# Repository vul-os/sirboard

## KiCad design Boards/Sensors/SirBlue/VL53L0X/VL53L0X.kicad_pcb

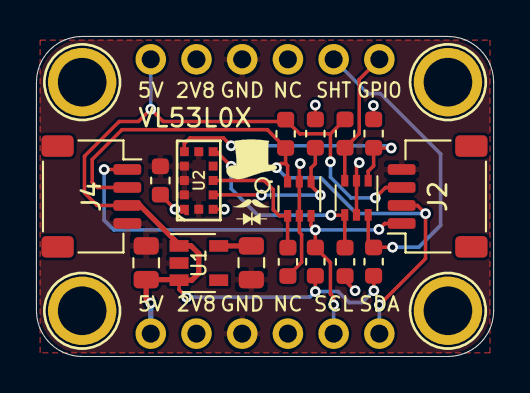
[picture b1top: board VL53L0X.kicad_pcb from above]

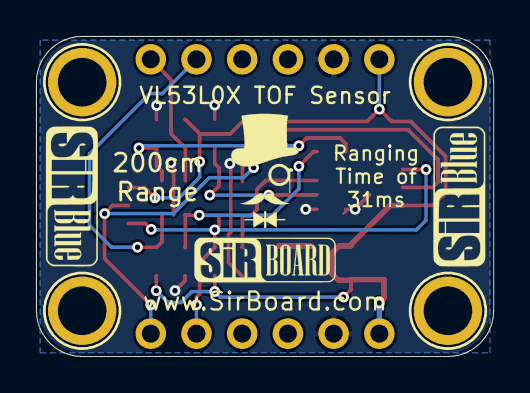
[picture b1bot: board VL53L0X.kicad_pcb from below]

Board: 2 copper layers, 25.4 x 17.8 mm, 23 parts (2 on the bottom side), 12 nets.

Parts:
C1, C4: 10uF; C_0805_2012Metric
C2: 100nF; C_0603_1608Metric
H1, H2, H3, H4: MountingHole; MountingHole_M2.5_SirBoard
J1, J3: Conn_01x06; PinHeader_1x06_P2.54mm_Vertical
J2, J4: Conn_01x04; JST_SH_SM04B-SRSS-TB_1x04-1MP_P1.00mm_Horizontal
Q1, Q2: BSS138DW; SOT-363_SC-70-6
R1, R2, R3, R4, R5, R6, R7, R8: 10K; R_0603_1608Metric
U1: AP2127K-2.8; SOT-23-5
U2: VL53L0X; LGA-12-2.4X4.4

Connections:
2V8: C2.1, J1.2, J3.2, Q1.2, Q1.5, Q2.2, Q2.5, R1.2, R3.2, R5.2, R7.2, U2.1, U2.11
5V: C1.1, J1.1, J2.3, J3.1, J4.3, R2.1, R4.1, R6.1, R8.1, U1.1, U1.3
GND: C1.2, C2.2, C4.2, J1.3, J2.4, J3.3, J4.4, U1.2, U2.2, U2.3, U2.4, U2.6, U2.12
GPIO_2V8: Q1.4, R3.1, U2.7
GPIO_5V: J3.6, Q1.3, R4.2
unnamed: C4.1, U1.5
SCL_2V8: Q2.1, R5.1, U2.10
SCL_5V: J1.5, J2.1, J4.1, Q2.6, R6.2
SDA_2V8: Q2.4, R7.1, U2.9
SDA_5V: J1.6, J2.2, J4.2, Q2.3, R8.2
XSHUT_2V8: Q1.1, R1.1, U2.5
XSHUT_5V: J3.5, Q1.6, R2.2

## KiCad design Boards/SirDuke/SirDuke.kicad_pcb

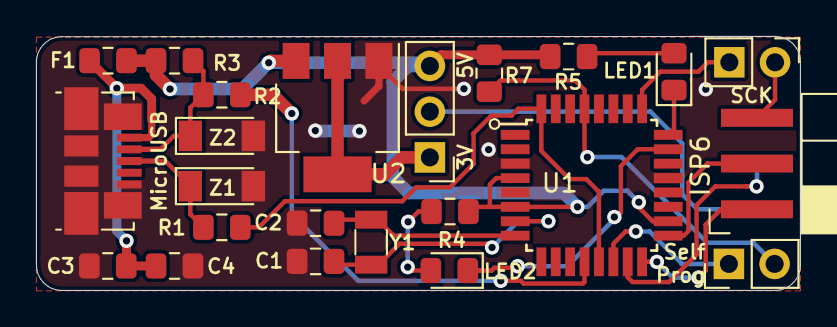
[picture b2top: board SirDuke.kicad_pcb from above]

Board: 2 copper layers, 42.4 x 14.1 mm, 23 parts (0 on the bottom side), 22 nets.

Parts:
3V      5V: Conn_01x03; PinHeader_1x03_P2.54mm_Vertical
C1, C2: 18pF; C_0805_2012Metric_Pad1.15x1.40mm_HandSolder
C3: 100nF; C_0805_2012Metric_Pad1.15x1.40mm_HandSolder
C4: 4u7; C_0805_2012Metric_Pad1.15x1.40mm_HandSolder
F1: 500mA; R_0805_2012Metric_Pad1.15x1.40mm_HandSolder
ISP6: Conn_02x03_Odd_Even; PinSocket_2x03_P2.54mm_Horizontal_SMD
LED1: G; LED_0805_2012Metric_Pad1.15x1.40mm_HandSolder
LED2: R; LED_0805_2012Metric_Pad1.15x1.40mm_HandSolder
MicroUSB: USB_B_Micro; USB_Micro-B_Molex_47346-0001
R1, R2: 68e; R_0805_2012Metric_Pad1.15x1.40mm_HandSolder
R3: 2k2; R_0805_2012Metric_Pad1.15x1.40mm_HandSolder
R4, R5: 1k; R_0805_2012Metric_Pad1.15x1.40mm_HandSolder
R7: 10k; R_0805_2012Metric_Pad1.15x1.40mm_HandSolder
SCK: Conn_01x02; PinHeader_1x02_P2.54mm_Vertical
SelfProg: Conn_01x02; PinHeader_1x02_P2.54mm_Vertical
U1: ATmega8-16AU; TQFP-32_7x7mm_P0.8mm
U2: AMS1117-3.3; SOT-223-3_TabPin2
Y1: Crystal; Crystal_SMD_3215-2Pin_3.2x1.5mm
Z1, Z2: 3.6V; D_MiniMELF

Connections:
unnamed: C1.1, C2.2, C3.2, C4.2, ISP6.6, MicroUSB.5, MicroUSB.6, U1.3, U1.5, U1.21, U2.1, Z1.2, Z2.2
unnamed: C1.2, U1.7, Y1.1
unnamed: C2.1, U1.8, Y1.2
unnamed: C3.1, C4.1, F1.2, MicroUSB.1
unnamed: 3V 5V.3, F1.1, R3.1, R4.1, R5.1, R7.2, U1.4, U1.6, U1.18, U2.3
unnamed: 3V 5V.1, U2.2
unnamed: 3V 5V.2, ISP6.2
unnamed: ISP6.5, SCK.1
unnamed: SCK.2, U1.25
unnamed: SelfProg.1, U1.14
unnamed: R7.1, SelfProg.2, U1.29
unnamed: MicroUSB.2, R2.2, R3.2, Z2.1
unnamed: MicroUSB.3, R1.2, Z1.1
unnamed: ISP6.1, U1.16
unnamed: ISP6.3, U1.17
unnamed: ISP6.4, U1.15
unnamed: LED1.1, U1.24
unnamed: LED1.2, R5.2
unnamed: LED2.1, U1.23
unnamed: LED2.2, R4.2
unnamed: R1.1, U1.13, U1.32
unnamed: R2.1, U1.12

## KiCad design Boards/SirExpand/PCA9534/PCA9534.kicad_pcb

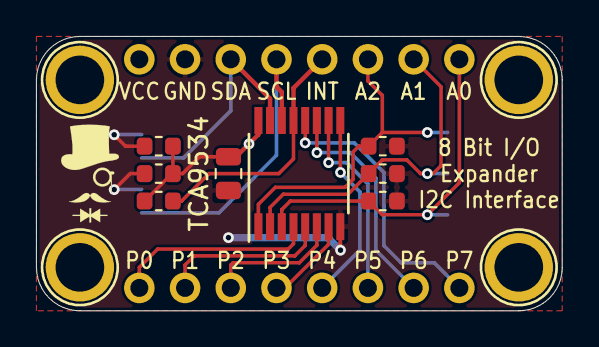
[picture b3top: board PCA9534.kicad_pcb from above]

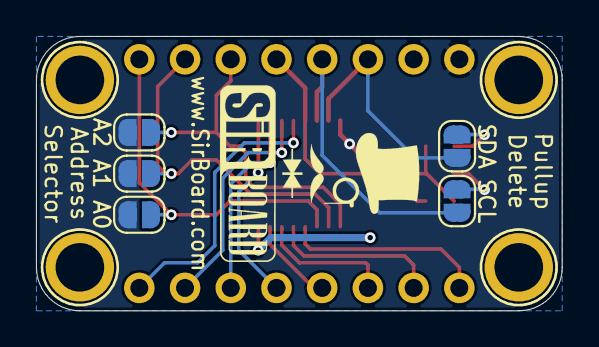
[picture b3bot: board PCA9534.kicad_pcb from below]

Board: 2 copper layers, 29.2 x 15.2 mm, 19 parts (5 on the bottom side), 18 nets.

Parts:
A0, A1, A2: SolderJumper_2_Open; SolderJumper-2_P1.3mm_Open_RoundedPad1.0x1.5mm
C1: 10uF; C_0805_2012Metric
H1, H2, H3, H4: MountingHole; MountingHole_M2.5_SirBoard
J1, J2: Conn_01x08; PinHeader_1x08_P2.54mm_Vertical
R1, R2, R3, R4, R5, R6: 10K; R_0603_1608Metric
SCL: SolderJumper_2_Open; SolderJumper-2_P1.3mm_Open_RoundedPad1.0x1.5mm
SDA: SolderJumper_2_Open; SolderJumper-2_P1.3mm_Open_RoundedPad1.0x1.5mm
TCA9534: TCA9534; TSSOP-16_4.4x5mm_P0.65mm

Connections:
A0: A0.1, J1.8, R1.1, TCA9534.3
A1: A1.1, J1.7, R4.1, TCA9534.2
A2: A2.1, J1.6, R5.1, TCA9534.1
GND: C1.2, J1.2, R1.2, R4.2, R5.2, TCA9534.8
INT: J1.5, R6.2, TCA9534.13
unnamed: R2.2, SCL.1
unnamed: R3.2, SDA.1
P0: J2.8, TCA9534.4
P1: J2.7, TCA9534.5
P2: J2.6, TCA9534.6
P3: J2.5, TCA9534.7
P4: J2.4, TCA9534.9
P5: J2.3, TCA9534.10
P6: J2.2, TCA9534.11
P7: J2.1, TCA9534.12
SCL: J1.4, SCL.2, TCA9534.14
SDA: J1.3, SDA.2, TCA9534.15
VCC: A0.2, A1.2, A2.2, C1.1, J1.1, R2.1, R3.1, R6.1, TCA9534.16

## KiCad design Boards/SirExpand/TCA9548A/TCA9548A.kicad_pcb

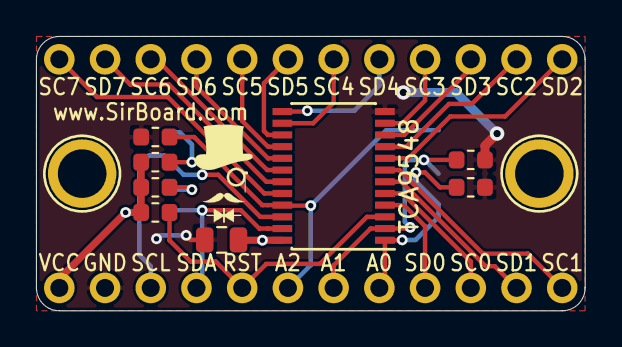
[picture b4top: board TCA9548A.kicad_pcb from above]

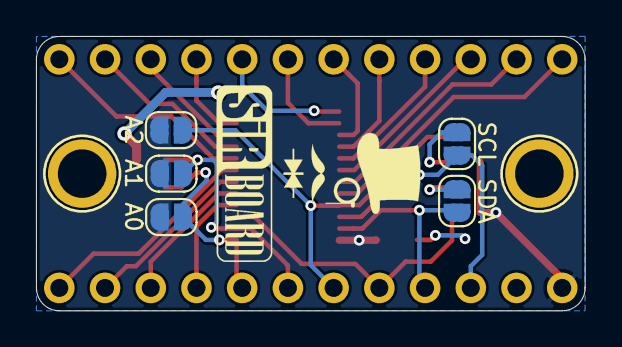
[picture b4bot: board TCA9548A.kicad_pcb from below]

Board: 2 copper layers, 30.5 x 15.2 mm, 15 parts (5 on the bottom side), 26 nets.

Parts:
A0, A1, A2: SolderJumper_2_Open; SolderJumper-2_P1.3mm_Open_RoundedPad1.0x1.5mm
C1: 10uF; C_0805_2012Metric
J1, J2: Conn_01x12; PinHeader_1x12_P2.54mm_Vertical
R1, R2, R3, R4, R5, R6: 10K; R_0603_1608Metric
SCL: SolderJumper_2_Open; SolderJumper-2_P1.3mm_Open_RoundedPad1.0x1.5mm
SDA: SolderJumper_2_Open; SolderJumper-2_P1.3mm_Open_RoundedPad1.0x1.5mm
TCA9548: TCA9548APWR; TSSOP-24_4.4x7.8mm_P0.65mm

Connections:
A0: A0.1, J1.8, R1.1, TCA9548.1
A1: A1.1, J1.7, R4.1, TCA9548.2
A2: A2.1, J1.6, R5.1, TCA9548.21
GND: C1.2, J1.2, R1.2, R4.2, R5.2, TCA9548.12
unnamed: R2.2, SCL.1
unnamed: R3.2, SDA.1
RST: J1.5, R6.2, TCA9548.3
SCL: J1.3, SCL.2, TCA9548.22
SCL0: J1.10, TCA9548.5
SCL1: J1.12, TCA9548.7
SCL2: J2.11, TCA9548.9
SCL3: J2.9, TCA9548.11
SCL4: J2.7, TCA9548.14
SCL5: J2.5, TCA9548.16
SCL6: J2.3, TCA9548.18
SCL7: J2.1, TCA9548.20
SDA: J1.4, SDA.2, TCA9548.23
SDA0: J1.9, TCA9548.4
SDA1: J1.11, TCA9548.6
SDA2: J2.12, TCA9548.8
SDA3: J2.10, TCA9548.10
SDA4: J2.8, TCA9548.13
SDA5: J2.6, TCA9548.15
SDA6: J2.4, TCA9548.17
SDA7: J2.2, TCA9548.19
VCC: A0.2, A1.2, A2.2, C1.1, J1.1, R2.1, R3.1, R6.1, TCA9548.24

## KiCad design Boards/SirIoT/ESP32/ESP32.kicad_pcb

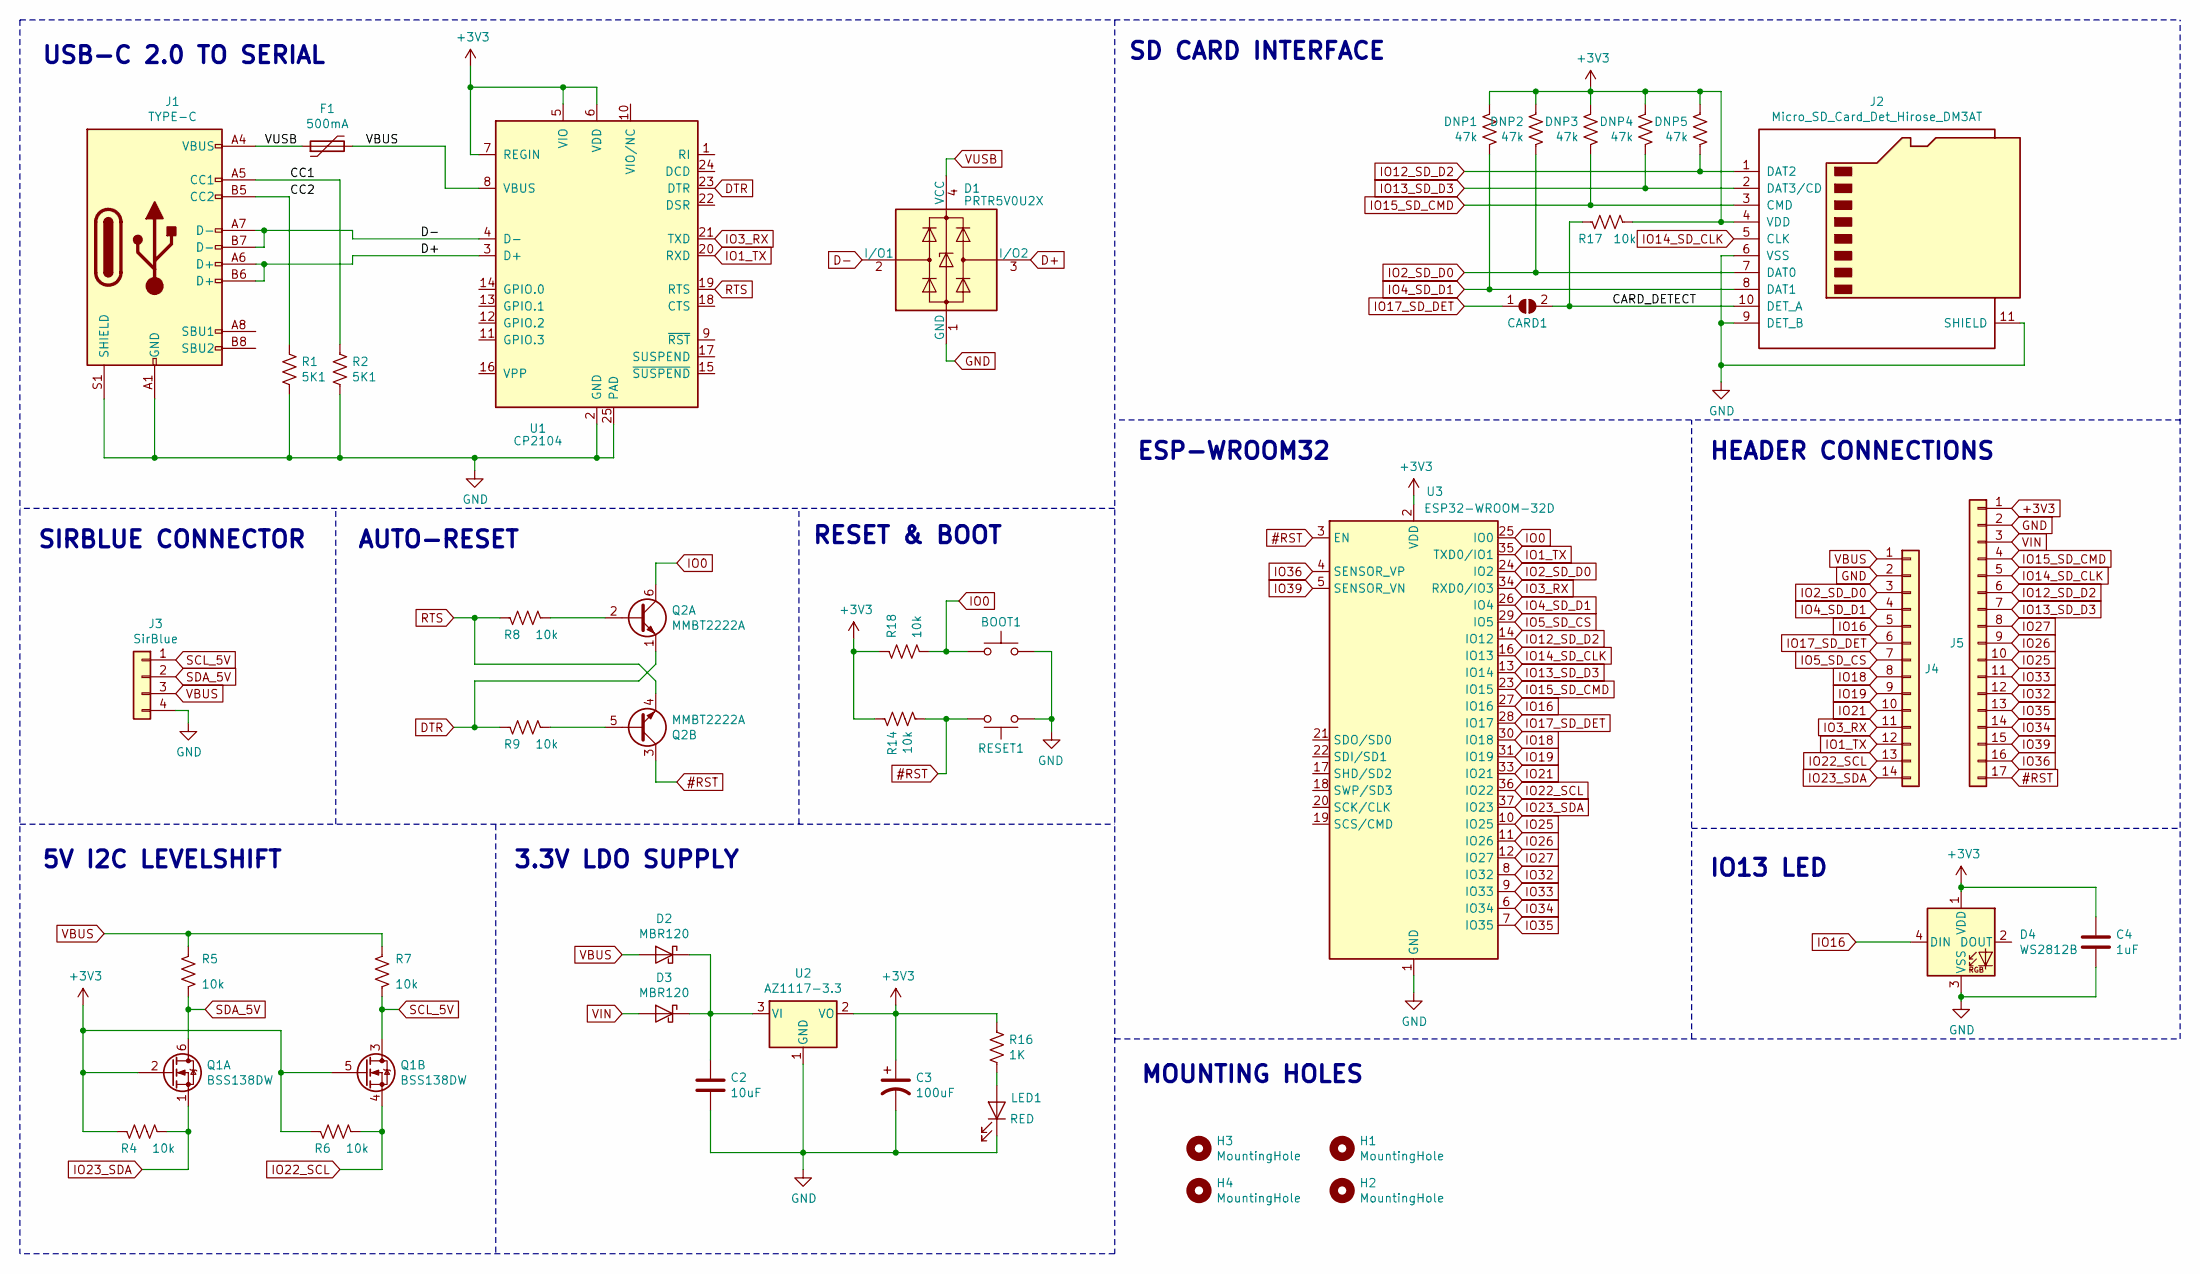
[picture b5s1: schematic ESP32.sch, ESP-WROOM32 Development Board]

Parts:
BOOT1: SW_Push; SW_SPST_B3U-1000P
C2: 10uF; C_0805_2012Metric; Part C95841
C3: 100uF; CP_EIA-3528-21_Kemet-B
C4: 1uF; C_0603_1608Metric; Part C29936
CARD1: SolderJumper_2_Open; SolderJumper-2_P1.3mm_Open_RoundedPad1.0x1.5mm
D1: PRTR5V0U2X; SOT-143; Part C12333
D2, D3: MBR120; D_SOD-123F; Part C223608
D4: WS2812B; LED_SK6812MINI_PLCC4_3.5x3.5mm_P1.75mm; Part C114583
DNP1, DNP2, DNP3, DNP4, DNP5: 47k; R_0805_2012Metric; Part C99198
F1: 500mA; Fuse_0805_2012Metric; Part C89657
H1, H2, H3, H4: MountingHole; MountingHole_2.7mm_M2.5
J1: TYPE-C; USB_C; Part C165948
J2: Micro_SD_Card_Det_Hirose_DM3AT; microSD_Hirose_DM3AT; Part C114218
J3: SirBlue; SirBlue_Connector; Part C160404
J4: Conn_01x14; PinHeader_1x14_P2.54mm_Vertical
J5: Conn_01x17; PinHeader_1x17_P2.54mm_Vertical
LED1: RED; LED_0603_1608Metric; Part C118330
Q1: BSS138DW; SOT-363_SC-70-6; Part C193381
Q2: MMBT2222A; SOT-363_SC-70-6
R1, R2: 5K1; R_0603_1608Metric; Part C332117
R4, R5, R6, R7, R8, R9, R14, R17, R18: 10k; R_0603_1608Metric; Part C99198
R16: 1K; R_0603_1608Metric; Part C25585
RESET1: SW_Push; SW_SPST_B3U-1000P
U1: CP2104; QFN-24-1EP_4x4mm_P0.5mm_EP2.6x2.6mm; Part C47742
U2: AZ1117-3.3; SOT-223-3_TabPin2; Part C108494
U3: ESP32-WROOM-32D; ESP32-WROOM-32

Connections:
#RST: J5.17, Q2.3 (C2), R14.2, RESET1.1, U3.3 (EN); also elsewhere on the board
+3V3: C3.1, C4.1, D4.1 (VDD), DNP1.1, DNP2.1, DNP3.1, DNP4.1, DNP5.1, J2.4 (VDD), J5.1, Q1.2 (G), Q1.5 (G), R4.1, R6.1, R14.1, R16.1, R17.2, R18.2, U1.5 (VIO), U1.6 (VDD), U1.7 (REGIN), U2.2 (VO), U3.2 (VDD)
/CARD_DETECT: CARD1.2 (B), J2.10 (DET_A), R17.1
/CC1: J1.A5 (CC1), R2.1
/CC2: J1.B5 (CC2), R1.1
D+: D1.3 (I/O2), J1.A6 (D+), J1.B6 (D+), U1.3 (D+)
D-: D1.2 (I/O1), J1.A7 (D-), J1.B7 (D-), U1.4 (D-)
DTR: Q2.1 (E1), R9.1, U1.23 (DTR)
GND: BOOT1.1, C2.2, C3.2, C4.2, D1.1 (GND), D4.3 (VSS), J1.A1 (GND), J1.A12 (GND), J1.B1 (GND), J1.B12 (GND), J1.S1 (SHIELD), J2.6 (VSS), J2.9 (DET_B), J2.11 (SHIELD), J3.4, J4.2, J5.2, LED1.1 (K), R1.2, R2.2, RESET1.2, U1.2 (GND), U1.25 (PAD), U2.1 (GND), U3.1 (GND), U3.15 (GND), U3.38 (GND); also elsewhere on the board
IO0: BOOT1.2, Q2.6 (C1), R18.1, U3.25 (IO0); also elsewhere on the board
IO1_TX: J4.12, U1.20 (RXD), U3.35 (TXD0/IO1)
IO2_SD_D0: DNP2.2, J2.7 (DAT0), J4.3, U3.24 (IO2)
IO3_RX: J4.11, U1.21 (TXD), U3.34 (RXD0/IO3)
IO4_SD_D1: DNP1.2, J2.8 (DAT1), J4.4, U3.26 (IO4)
IO5_SD_CS: J4.7, U3.29 (IO5)
IO12_SD_D2: DNP5.2, J2.1 (DAT2), J5.6, U3.14 (IO12)
IO13_SD_D3: DNP4.2, J2.2 (DAT3/CD), J5.7, U3.13 (IO14)
IO14_SD_CLK: J2.5 (CLK), J5.5, U3.16 (IO13)
IO15_SD_CMD: DNP3.2, J2.3 (CMD), J5.4, U3.23 (IO15)
IO16: D4.4 (DIN), J4.5, U3.27 (IO16)
IO17_SD_DET: CARD1.1 (A), J4.6, U3.28 (IO17)
IO18: J4.8, U3.30 (IO18)
IO19: J4.9, U3.31 (IO19)
IO21: J4.10, U3.33 (IO21)
IO22_SCL: J4.13, Q1.4 (S), R6.2, U3.36 (IO22)
IO23_SDA: J4.14, Q1.1 (S), R4.2, U3.37 (IO23)
IO25: J5.10, U3.10 (IO25)
IO26: J5.9, U3.11 (IO26)
IO27: J5.8, U3.12 (IO27)
IO32: J5.12, U3.8 (IO32)
IO33: J5.11, U3.9 (IO33)
IO34: J5.14, U3.6 (IO34)
IO35: J5.13, U3.7 (IO35)
IO36: J5.16, U3.4 (SENSOR_VP)
IO39: J5.15, U3.5 (SENSOR_VN)
unnamed: C2.1, D2.1 (K), D3.1 (K), U2.3 (VI)
unnamed 39: LED1.2 (A), R16.2; also elsewhere on the board
unnamed: Q2.2 (B1), R8.2
unnamed: Q2.5 (B2), R9.2
RTS: Q2.4 (E2), R8.1, U1.19 (RTS)
SCL_5V: J3.1, Q1.3 (D), R7.1; also elsewhere on the board
SDA_5V: J3.2, Q1.6 (D), R5.1; also elsewhere on the board
VBUS: D2.2 (A), F1.2, J3.3, J4.1, R5.2, R7.2, U1.8 (VBUS); also elsewhere on the board
VIN: D3.2 (A), J5.3
VUSB: D1.4 (VCC), F1.1, J1.A4 (VBUS), J1.A9 (VBUS), J1.B4 (VBUS), J1.B9 (VBUS)

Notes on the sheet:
3.3V LDO SUPPLY
USB-C 2.0 TO SERIAL
AUTO-RESET
5V I2C LEVELSHIFT
RESET & BOOT
ESP-WROOM32
SD CARD INTERFACE
IO13 LED
HEADER CONNECTIONS
MOUNTING HOLES
SIRBLUE CONNECTOR

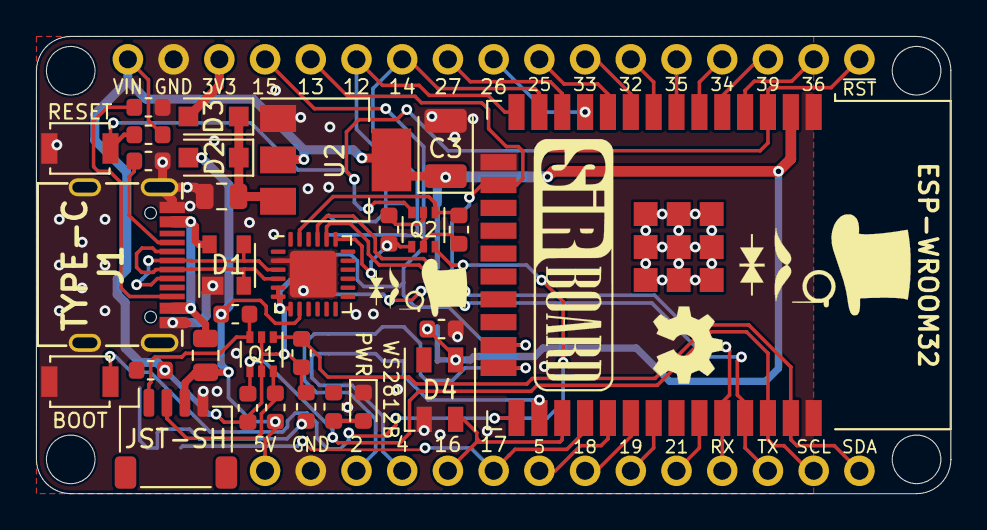
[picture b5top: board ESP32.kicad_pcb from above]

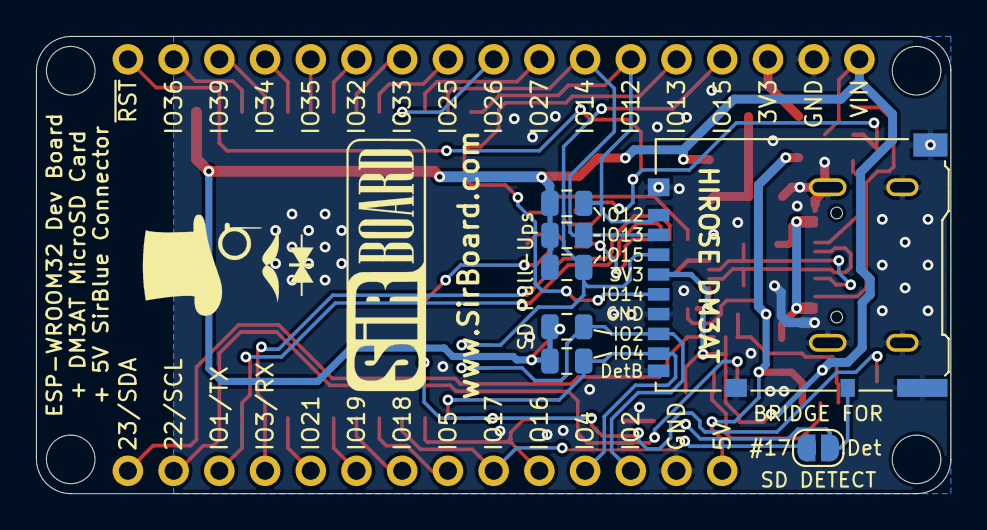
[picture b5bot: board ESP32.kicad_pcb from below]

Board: 2 copper layers, 50.8 x 25.4 mm, 43 parts (9 on the bottom side), 45 nets.

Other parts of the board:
BOOT: SW_Push; SW_SPST_B3U-1000P
JST-SH: SirBlue; SirBlue_Connector
PWR: RED; LED_0603_1608Metric
RESET: SW_Push; SW_SPST_B3U-1000P

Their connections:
#RST: RESET.1; also elsewhere on the board
GND: BOOT.1, JST-SH.4, PWR.1, RESET.2; also elsewhere on the board
IO0: BOOT.2; also elsewhere on the board
unnamed 39: PWR.2; also elsewhere on the board
SCL_5V: JST-SH.1; also elsewhere on the board
SDA_5V: JST-SH.2; also elsewhere on the board
VBUS: JST-SH.3; also elsewhere on the board

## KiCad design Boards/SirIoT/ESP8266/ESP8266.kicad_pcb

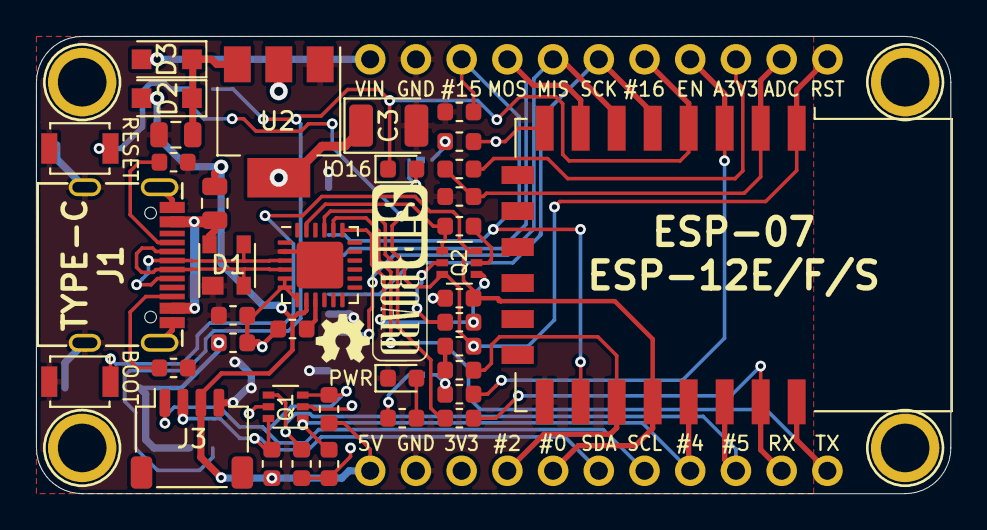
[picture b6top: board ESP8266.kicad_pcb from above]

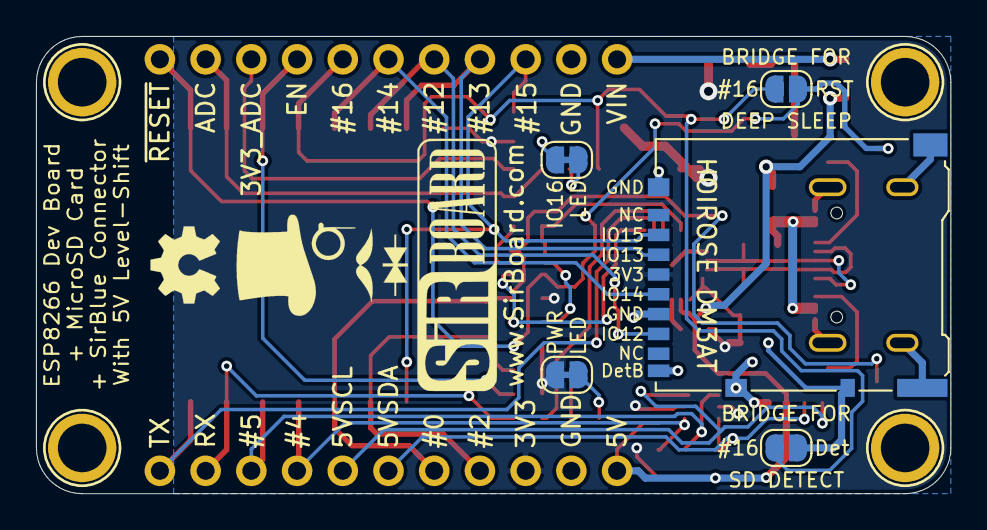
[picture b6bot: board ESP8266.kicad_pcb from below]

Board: 2 copper layers, 50.8 x 25.4 mm, 49 parts (7 on the bottom side), 38 nets.

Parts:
BOOT: SW_Push; SW_SPST_B3U-1000P
C1: 100nF; C_0603_1608Metric
C2: 10uF; C_0805_2012Metric
C3: 100uF; CP_EIA-3528-21_Kemet-B
CARD1: SolderJumper_2_Open; SolderJumper-2_P1.3mm_Open_RoundedPad1.0x1.5mm
D1: PRTR5V0U2X; SOT-143
D2, D3: MBR120; D_SOD-123F
F1: 500mA; Fuse_0805_2012Metric
H1, H2, H3, H4: MountingHole; MountingHole_M2.5_SirBoard
HOIROSE DM3AT: Micro_SD_Card_Det_Hirose_DM3AT; microSD_Hirose_DM3AT
IO16: LED_DELETE2; SolderJumper-2_P1.3mm_Bridged_RoundedPad1.0x1.5mm
IO16#2: BLUE; LED_0603_1608Metric
J1: TYPE-C; USB_C
J3: SirBlue; SirBlue_Connector
J4, J6: Conn_01x11; PinHeader_1x11_P2.54mm_Vertical
PWR: LED_DELETE1; SolderJumper-2_P1.3mm_Bridged_RoundedPad1.0x1.5mm
PWR#2: RED; LED_0603_1608Metric
Q1: BSS138DW; SOT-363_SC-70-6
Q2: MMBT2222A; SOT-363_SC-70-6
R1, R2: 5K1; R_0603_1608Metric
R3: 4K7; R_0603_1608Metric
R4, R5, R6, R7, R8, R9, R10, R11, R14, R17, R18: 10k; R_0603_1608Metric
R12, R15, R16: 1K; R_0603_1608Metric
R13: 10K; R_0603_1608Metric
R19: 220K; R_0603_1608Metric
R20: 100K; R_0603_1608Metric
RESET: SW_Push; SW_SPST_B3U-1000P
SLEEP1: SolderJumper_2_Open; SolderJumper-2_P1.3mm_Open_RoundedPad1.0x1.5mm
U1: CP2104; QFN-24-1EP_4x4mm_P0.5mm_EP2.6x2.6mm
U2: AZ1117-3.3; SOT-223-3_TabPin2
U3: ESP-12F; ESP-12E

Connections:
#RST: J6.11, Q2.3, R14.2, RESET.1, SLEEP1.2, U3.1
+3V3: C1.1, C3.1, HOIROSE DM3AT.4, J4.3, PWR.1, Q1.2, Q1.5, R3.2, R4.1, R6.1, R10.2, R11.2, R14.1, R15.1, R17.1, R18.2, U1.5, U1.6, U1.7, U2.2, U3.8
/CARD_DETECT: CARD1.2, HOIROSE DM3AT.10, R17.2
/CC1: J1.A5, R2.1
/CC2: J1.B5, R1.1
/RST: R3.1, U1.9
ADC: J6.10, R19.1, R20.2, U3.2
ADC_3V3: J6.9, R19.2
D+: D1.3, J1.A6, J1.B6, U1.3
D-: D1.2, J1.A7, J1.B7, U1.4
DTR: Q2.1, R9.1, U1.23
EN: J6.8, R10.1, U3.3
GND: BOOT.1, C1.2, C2.2, C3.2, D1.1, HOIROSE DM3AT.6, HOIROSE DM3AT.9, HOIROSE DM3AT.11, J1.A1, J1.A12, J1.B1, J1.B12, J1.S1, J3.4, J4.2, J6.2, PWR#2.1, R1.2, R2.2, R13.1, R20.1, RESET.2, U1.2, U1.25, U2.1, U3.15
GPIO0: BOOT.2, J4.5, Q2.6, R18.1, U3.18
GPIO2: J4.4, R11.1, U3.17
GPIO12_MISO: HOIROSE DM3AT.7, J6.5, U3.6
GPIO13_MOSI: HOIROSE DM3AT.3, J6.4, U3.7
GPIO14_SCK: HOIROSE DM3AT.5, J6.6, U3.5
GPIO15: HOIROSE DM3AT.2, J6.3, R13.2, U3.16
GPIO16: CARD1.1, IO16#2.1, J6.7, SLEEP1.1, U3.4
unnamed: C2.1, D2.1, D3.1, U2.3
unnamed: PWR.2, R16.1
unnamed: IO16.1, R15.2
unnamed: IO16.2, IO16#2.2
unnamed: PWR#2.2, R16.2
unnamed: Q2.2, R8.2
unnamed: Q2.5, R9.2
RTS: Q2.4, R8.1, U1.19
RXD: J4.10, R12.2, U3.21
RX_ESP: R12.1, U1.21
SCL_3V3: J4.9, Q1.4, R6.2, U3.20
SCL_5V: J3.1, J4.7, Q1.3, R7.1
SDA_3V3: J4.8, Q1.1, R4.2, U3.19
SDA_5V: J3.2, J4.6, Q1.6, R5.1
TX_ESP: J4.11, U1.20, U3.22
VBUS: D2.2, F1.2, J3.3, J4.1, R5.2, R7.2, U1.8
VIN: D3.2, J6.1
VUSB: D1.4, F1.1, J1.A4, J1.A9, J1.B4, J1.B9

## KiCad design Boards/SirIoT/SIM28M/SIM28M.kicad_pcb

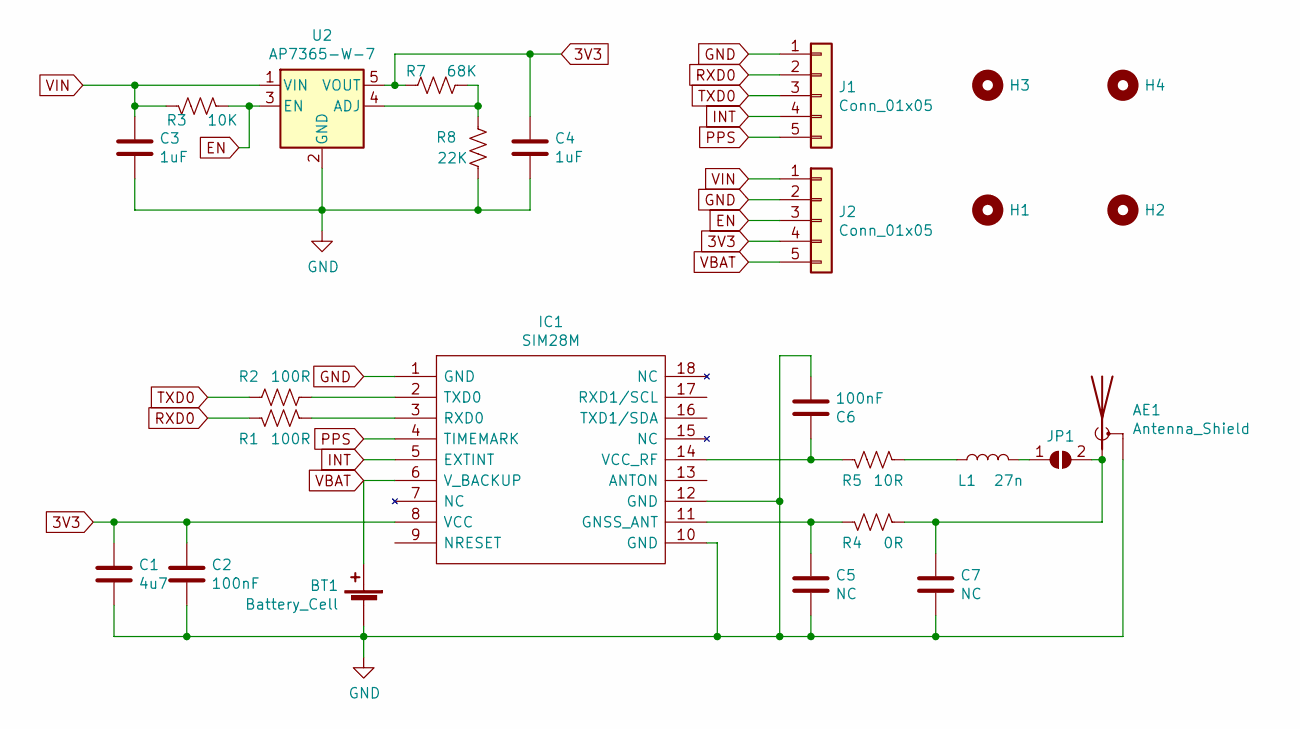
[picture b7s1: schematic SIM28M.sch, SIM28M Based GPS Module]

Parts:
AE1: Antenna_Shield; U.FL_Hirose_U.FL-R-SMT-1_Vertical
BT1: Battery_Cell; BatteryHolder_Keystone_3000_1x12mm
C1: 4u7; C_0805_2012Metric
C2, C6: 100nF; C_0603_1608Metric
C3, C4: 1uF; C_0805_2012Metric
C5, C7: NC; C_0603_1608Metric
H1, H2, H3, H4: MountingHole; MountingHole_2.7mm_M2.5_ISO14580_Pad
IC1: SIM28M; Manufacturer_Part_Number SIM28M
J1, J2: Conn_01x05; PinHeader_1x05_P2.54mm_Vertical
JP1: SolderJumper_2_Open; SolderJumper-2_P1.3mm_Open_RoundedPad1.0x1.5mm
L1: 27n; L_0603_1608Metric
R1, R2: 100R; R_0603_1608Metric
R3: 10K; R_0603_1608Metric
R4: 0R; R_0603_1608Metric
R5: 10R; R_0603_1608Metric
R7: 68K; R_0603_1608Metric
R8: 22K; R_0603_1608Metric
U2: AP7365-W-7; SOT-23-5

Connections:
3V3: C1.1, C2.1, C4.1, IC1.8 (VCC), J2.4, R7.1, U2.5 (VOUT); also elsewhere on the board
EN: J2.3, R3.2, U2.3 (EN)
GND: AE1.2 (Shield), BT1.2 (-), C1.2, C2.2, C3.2, C4.2, C5.2, C6.2, C7.2, IC1.1 (GND), IC1.10 (GND), IC1.12 (GND), J1.1, J2.2, R8.1, U2.2 (GND); also elsewhere on the board
INT: IC1.5 (EXTINT), J1.4; also elsewhere on the board
unnamed: AE1.1 (A), C7.1, JP1.2 (B), R4.2
unnamed 5: C5.1, IC1.11 (GNSS_ANT), R4.1; also elsewhere on the board
unnamed 6: C6.1, IC1.14 (VCC_RF), R5.1; also elsewhere on the board
unnamed 7: IC1.2 (TXD0), R2.2; also elsewhere on the board
unnamed 8: IC1.3 (RXD0), R1.2; also elsewhere on the board
unnamed: JP1.1 (A), L1.1
unnamed: L1.2, R5.2
unnamed: R7.2, R8.2, U2.4 (ADJ)
PPS: IC1.4 (TIMEMARK), J1.5; also elsewhere on the board
RXD0: J1.2, R1.1
TXD0: J1.3, R2.1
VBAT: BT1.1 (+), IC1.6 (V_BACKUP), J2.5; also elsewhere on the board
VIN: C3.1, J2.1, R3.1, U2.1 (VIN)

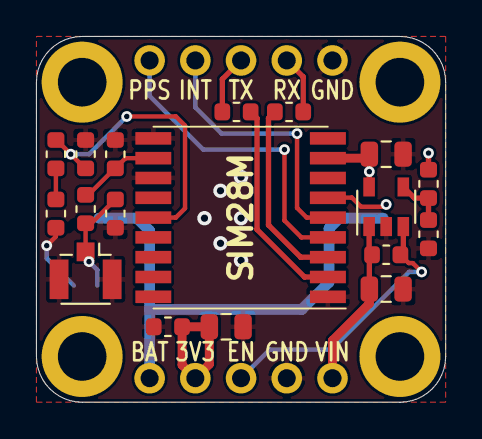
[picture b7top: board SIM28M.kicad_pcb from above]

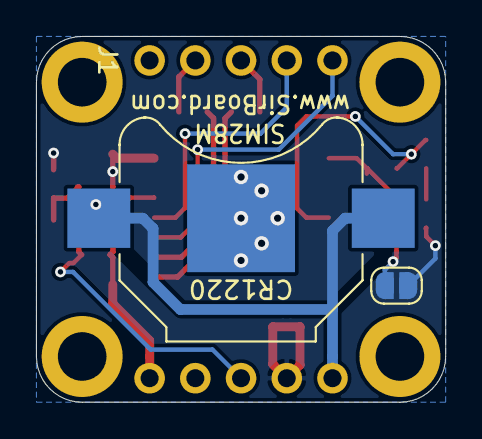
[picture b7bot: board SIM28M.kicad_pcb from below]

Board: 2 copper layers, 22.7 x 20.3 mm, 26 parts (4 on the bottom side), 17 nets.

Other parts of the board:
CR1220: Battery_Cell; BatteryHolder_Keystone_3000_1x12mm
SIM28M: SIM28M

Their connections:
3V3: SIM28M.8; also elsewhere on the board
GND: CR1220.2, SIM28M.1, SIM28M.10, SIM28M.12; also elsewhere on the board
INT: SIM28M.5; also elsewhere on the board
unnamed 5: SIM28M.11; also elsewhere on the board
unnamed 6: SIM28M.14; also elsewhere on the board
unnamed 7: SIM28M.2; also elsewhere on the board
unnamed 8: SIM28M.3; also elsewhere on the board
PPS: SIM28M.4; also elsewhere on the board
VBAT: CR1220.1, SIM28M.6; also elsewhere on the board

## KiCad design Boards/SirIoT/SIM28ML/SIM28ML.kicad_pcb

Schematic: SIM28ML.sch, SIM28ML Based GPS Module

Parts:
AE1: Antenna_Shield; U.FL_Hirose_U.FL-R-SMT-1_Vertical; Part C88374
BT1: Battery_Cell; S8411-45R_1; Part C70381
C1: 4.7uF; C_0603_1608Metric
C2: 100nF; C_0603_1608Metric; Part C42998
C3, C4: 10uF; C_0805_2012Metric; Part C95841
C5, C7: NC; C_0603_1608Metric
D1: LED; LED_0603_1608Metric; Part C193191
H1, H2, H3, H4: MountingHole; MountingHole_M2.5_SirBoard
IC1: SIM28M; Manufacturer_Part_Number SIM28M
J1, J2: Conn_01x05; PinHeader_1x05_P2.54mm_Vertical
JP2: SolderJumper_2_Bridged; SolderJumper-2_P1.3mm_Bridged_RoundedPad1.0x1.5mm
R1, R2: 100R; R_0603_1608Metric; Part C245184
R3: 10K; R_0603_1608Metric; Part C99198
R4: 0R; R_0603_1608Metric; Part C269698
R6: 680E; R_0603_1608Metric; Part C269441
U1: AP2127K-3.3; SOT-23-5

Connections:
3V3: C1.1, C2.1, C4.1, IC1.8, J2.4, JP2.1 (A), U1.5 (VOUT)
/ANT: C5.1, IC1.11, R4.1
EN: J2.3, R3.2, U1.3 (EN)
GND: AE1.2 (Shield), BT1.2 (-), C1.2, C2.2, C3.2, C4.2, C5.2, C7.2, D1.1 (K), IC1.1, IC1.10, IC1.12, J1.5, J2.2, U1.2 (GND); also elsewhere on the board
INT: IC1.5, J1.4
unnamed: AE1.1 (A), C7.1, R4.2
unnamed 6: D1.2 (A), R6.1; also elsewhere on the board
unnamed: IC1.2, R2.2
unnamed: IC1.3, R1.2
unnamed: JP2.2 (B), R6.2
PPS: IC1.4, J1.3
RXD0: J1.2, R1.1
TXD0: J1.1, R2.1
VBAT: BT1.1 (+), IC1.6, J2.5
VIN: C3.1, J2.1, R3.1, U1.1 (VIN)

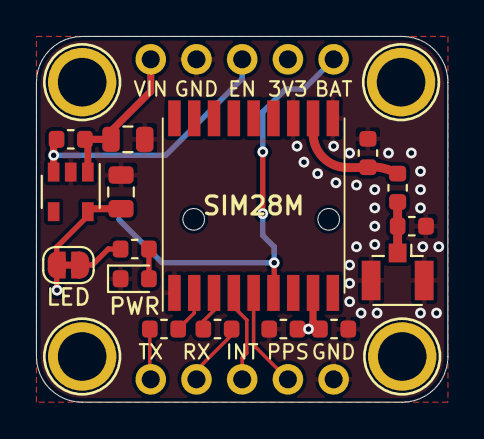
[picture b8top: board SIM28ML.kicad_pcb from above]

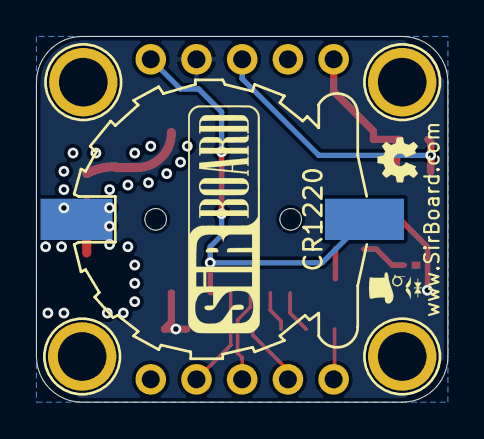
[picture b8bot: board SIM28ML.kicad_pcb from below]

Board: 2 copper layers, 22.9 x 20.3 mm, 23 parts (3 on the bottom side), 15 nets.

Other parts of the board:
PWR: LED; LED_0603_1608Metric

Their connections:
GND: PWR.1; also elsewhere on the board
unnamed 6: PWR.2; also elsewhere on the board
